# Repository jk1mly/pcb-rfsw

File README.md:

SkyworksのSKY13453-385LFを使うための基板
パッケージが1mm角と小さいデバイスだが、手半田（リフローしない）で付けられるようパッドを工夫
IC以外はチップ部品せず、デバイスが半田できるか試す＋使い方の確認用

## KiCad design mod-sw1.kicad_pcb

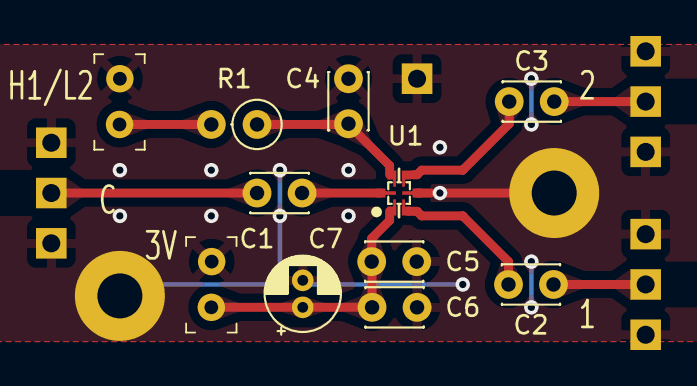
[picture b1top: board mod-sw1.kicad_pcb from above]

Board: 2 copper layers, 23 parts (0 on the bottom side), 10 nets.

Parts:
C1, C2, C3, C4, C5, C6: C; C_Disc_D3.0mm_W2.0mm_P2.50mm
C7: 10u; CP_Radial_D4.0mm_P1.50mm
J1, J2, J3, J4, J5, J6: Conn_01x01_Pin; PinHeader_1x01
J7, J8, J9, J10: G; PinHeader_1x01
J11, J12: Conn_01x02_Male; PinHeader_1x2_P2.54mm
R1: 10; R_Axial_DIN0207_L6.3mm_D2.5mm_P2.54mm_Vertical
TP1, TP2: TestPoint; MountingHole_2.5mm_Pad
U1: SKY13453-385LF; QFN6_1x1mm

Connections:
+5V: C5.1, C6.1, C7.1, J12.1, U1.1 (VDD)
GND: C4.2, C5.2, C6.2, C7.2, J2.1, J4.1, J6.1, J7.1, J8.1, J9.1, J10.1, J11.2, J12.2, TP1.1, TP2.1, U1.3 (GND)
unnamed: C1.1, J1.1
unnamed: C2.1, J3.1
unnamed: C3.2, J5.1
unnamed: J11.1, R1.2
unnamed: C2.2, U1.2 (RF1)
unnamed: C3.1, U1.4 (RF2)
unnamed: C1.2, U1.6 (RFC)
unnamed: C4.1, R1.1, U1.5 (VCTL)
